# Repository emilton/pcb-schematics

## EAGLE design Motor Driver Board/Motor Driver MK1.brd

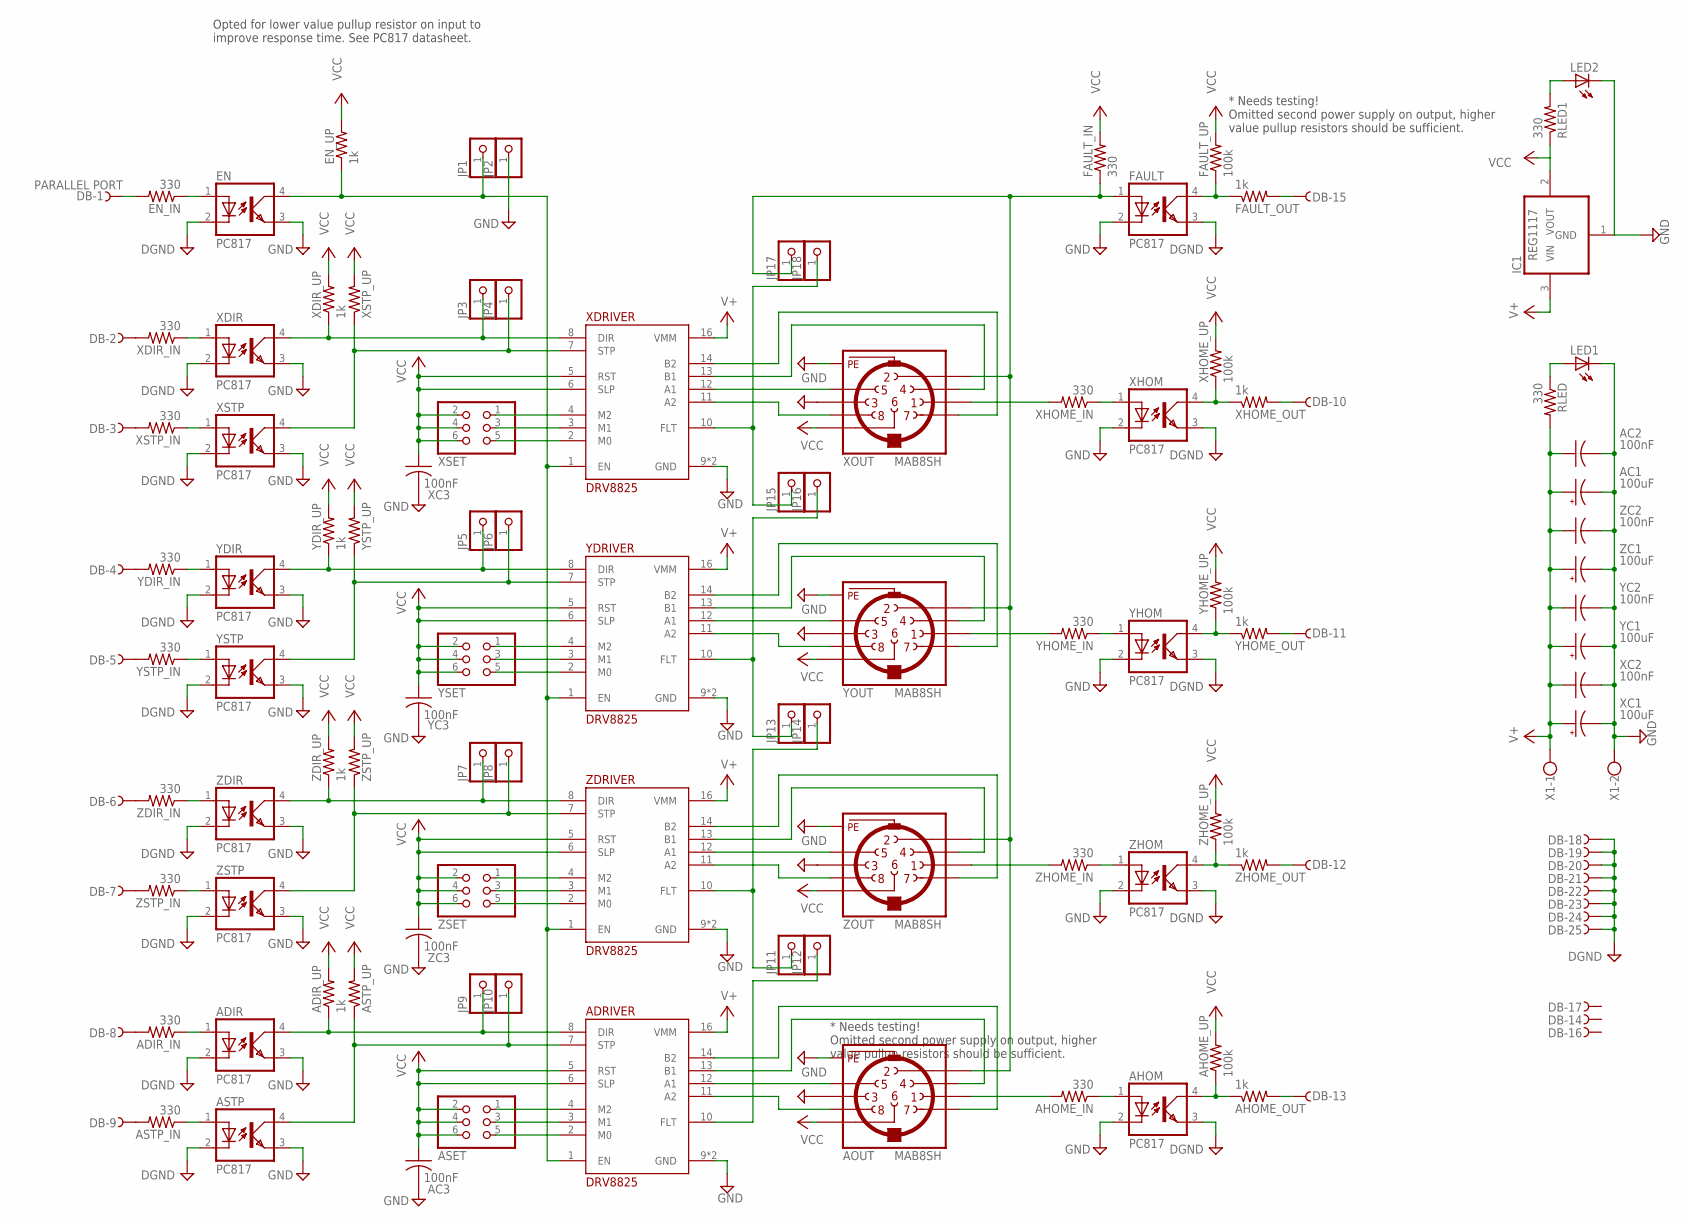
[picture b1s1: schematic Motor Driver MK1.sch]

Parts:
AC1: 100uF; SANYO-OSCON_SMD_E7
AC2, AC3: 100nF; C0805
ADIR: PC817; DIL04
ADIR_IN: 330; R0805
ADIR_UP: 1k; R0805
ADRIVER: DRV8825; DIP16
AHOM: PC817; DIL04
AHOME_IN: 330; R0805
AHOME_OUT: 1k; R0805
AHOME_UP: 100k; R0805
AOUT: MAB8SH
ASET: PINHD-2X3; 2X03
ASTP: PC817; DIL04
ASTP_IN: 330; R0805
ASTP_UP: R-US_R0805; R0805
DB: PARALLEL PORT; H2R25ST
EN: PC817; DIL04
EN_IN: 330; R0805
EN_UP: 1k; R0805
FAULT: PC817; DIL04
FAULT_IN: 330; R0805
FAULT_OUT: 1k; R0805
FAULT_UP: 100k; R0805
IC1: REG1117; SOT223
JP1, JP2, JP3, JP4, JP5, JP6, JP7, JP8, JP9, JP10, JP11, JP12, JP13, JP14, JP15, JP16, JP17, JP18: PINHD-1X1; 1X01
LED1, LED2: LEDCHIP-LED0805; CHIP-LED0805
RLED, RLED1: 330; R0805
X1: W237-102
XC1: 100uF; SANYO-OSCON_SMD_E7
XC2, XC3: 100nF; C0805
XDIR: PC817; DIL04
XDIR_IN: 330; R0805
XDIR_UP: 1k; R0805
XDRIVER: DRV8825; DIP16
XHOM: PC817; DIL04
XHOME_IN: 330; R0805
XHOME_OUT: 1k; R0805
XHOME_UP: 100k; R0805
XOUT: MAB8SH
XSET: PINHD-2X3; 2X03
XSTP: PC817; DIL04
XSTP_IN: 330; R0805
XSTP_UP: R-US_R0805; R0805
YC1: 100uF; SANYO-OSCON_SMD_E7
YC2, YC3: 100nF; C0805
YDIR: PC817; DIL04
YDIR_IN: 330; R0805
YDIR_UP: 1k; R0805
YDRIVER: DRV8825; DIP16
YHOM: PC817; DIL04
YHOME_IN: 330; R0805
YHOME_OUT: 1k; R0805
YHOME_UP: 100k; R0805
YOUT: MAB8SH
YSET: PINHD-2X3; 2X03
YSTP: PC817; DIL04
YSTP_IN: 330; R0805
YSTP_UP: R-US_R0805; R0805
ZC1: 100uF; SANYO-OSCON_SMD_E7
ZC2, ZC3: 100nF; C0805
ZDIR: PC817; DIL04
ZDIR_IN: 330; R0805
ZDIR_UP: 1k; R0805
ZDRIVER: DRV8825; DIP16
ZHOM: PC817; DIL04
ZHOME_IN: 330; R0805
ZHOME_OUT: 1k; R0805
ZHOME_UP: 100k; R0805
ZOUT: MAB8SH
ZSET: PINHD-2X3; 2X03
ZSTP: PC817; DIL04
ZSTP_IN: 330; R0805
ZSTP_UP: R-US_R0805; R0805

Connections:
ASTP_UP: ADRIVER.7 (STP), ASTP.4 (COL), ASTP_UP.1, JP10.1
DGND: ADIR.2 (C), AHOM.3 (EMIT), ASTP.2 (C), DB.18, DB.19, DB.20, DB.21, DB.22, DB.23, DB.24, DB.25, EN.2 (C), FAULT.3 (EMIT), XDIR.2 (C), XHOM.3 (EMIT), XSTP.2 (C), YDIR.2 (C), YHOM.3 (EMIT), YSTP.2 (C), ZDIR.2 (C), ZHOM.3 (EMIT), ZSTP.2 (C)
GND: AC1.-, AC2.2, AC3.2, ADIR.3 (EMIT), ADRIVER.9 (GND), ADRIVER.15 (GND), AHOM.2 (C), AOUT.3, AOUT.PE, AOUT.PE@ (PE), ASTP.3 (EMIT), EN.3 (EMIT), FAULT.2 (C), IC1.1 (GND), JP2.1, LED1.C, LED2.C, X1.2, XC1.-, XC2.2, XC3.2, XDIR.3 (EMIT), XDRIVER.9 (GND), XDRIVER.15 (GND), XHOM.2 (C), XOUT.3, XOUT.PE, XOUT.PE@ (PE), XSTP.3 (EMIT), YC1.-, YC2.2, YC3.2, YDIR.3 (EMIT), YDRIVER.9 (GND), YDRIVER.15 (GND), YHOM.2 (C), YOUT.3, YOUT.PE, YOUT.PE@ (PE), YSTP.3 (EMIT), ZC1.-, ZC2.2, ZC3.2, ZDIR.3 (EMIT), ZDRIVER.9 (GND), ZDRIVER.15 (GND), ZHOM.2 (C), ZOUT.3, ZOUT.PE, ZOUT.PE@ (PE), ZSTP.3 (EMIT)
unnamed: XDRIVER.11 (A2), XOUT.8
unnamed: XDRIVER.12 (A1), XOUT.5
unnamed: XDRIVER.13 (B1), XOUT.4
unnamed: XDRIVER.14 (B2), XOUT.7
unnamed: ADRIVER.12 (A1), AOUT.5
unnamed: YDRIVER.12 (A1), YOUT.5
unnamed: YDRIVER.11 (A2), YOUT.8
unnamed: YDRIVER.13 (B1), YOUT.4
unnamed: YDRIVER.14 (B2), YOUT.7
unnamed: ZDRIVER.12 (A1), ZOUT.5
unnamed: ZDRIVER.11 (A2), ZOUT.8
unnamed: ZDRIVER.13 (B1), ZOUT.4
unnamed: ZDRIVER.14 (B2), ZOUT.7
unnamed: ADRIVER.11 (A2), AOUT.8
unnamed: ADRIVER.13 (B1), AOUT.4
unnamed: ADRIVER.14 (B2), AOUT.7
unnamed: JP4.1, XDRIVER.7 (STP), XSTP.4 (COL), XSTP_UP.1
unnamed: XDRIVER.4 (M2), XSET.1
unnamed: XDRIVER.3 (M1), XSET.3
unnamed: XDRIVER.2 (M0), XSET.5
unnamed: YDRIVER.4 (M2), YSET.1
unnamed: YDRIVER.3 (M1), YSET.3
unnamed: YDRIVER.2 (M0), YSET.5
unnamed: ADRIVER.4 (M2), ASET.1
unnamed: ADRIVER.3 (M1), ASET.3
unnamed: ADRIVER.2 (M0), ASET.5
unnamed: ZDRIVER.4 (M2), ZSET.1
unnamed: ZDRIVER.3 (M1), ZSET.3
unnamed: ZDRIVER.2 (M0), ZSET.5
unnamed: LED2.A, RLED1.2
unnamed: AHOM.1 (A), AHOME_IN.1
unnamed: EN.1 (A), EN_IN.1
unnamed: ADRIVER.1 (EN), EN.4 (COL), EN_UP.1, JP1.1, XDRIVER.1 (EN), YDRIVER.1 (EN), ZDRIVER.1 (EN)
unnamed: JP11.1, JP14.1, ZDRIVER.10 (FLT)
unnamed: XDIR.1 (A), XDIR_IN.1
unnamed: XSTP.1 (A), XSTP_IN.1
unnamed: YDIR.1 (A), YDIR_IN.1
unnamed: YSTP.1 (A), YSTP_IN.1
unnamed: DB.3, XSTP_IN.2
unnamed: DB.2, XDIR_IN.2
unnamed: DB.5, YSTP_IN.2
unnamed: DB.4, YDIR_IN.2
unnamed: ZSTP.1 (A), ZSTP_IN.1
unnamed: ZDIR.1 (A), ZDIR_IN.1
unnamed: AHOM.4 (COL), AHOME_OUT.1, AHOME_UP.1
unnamed: DB.6, ZDIR_IN.2
unnamed: ADIR.1 (A), ADIR_IN.1
unnamed: ASTP_IN.2, DB.9
unnamed: ADIR_IN.2, DB.8
unnamed: ASTP.1 (A), ASTP_IN.1
unnamed: DB.1, EN_IN.2
unnamed: DB.10, XHOME_OUT.2
unnamed: AOUT.2, FAULT.1 (A), FAULT_IN.1, JP17.1, XOUT.2, YOUT.2, ZOUT.2
unnamed: ADIR.4 (COL), ADIR_UP.1, ADRIVER.8 (DIR), JP9.1
unnamed: FAULT.4 (COL), FAULT_OUT.1, FAULT_UP.1
unnamed: DB.15, FAULT_OUT.2
unnamed: JP15.1, JP18.1, XDRIVER.10 (FLT)
unnamed: JP13.1, JP16.1, YDRIVER.10 (FLT)
unnamed: ADRIVER.10 (FLT), JP12.1
unnamed: XHOM.4 (COL), XHOME_OUT.1, XHOME_UP.1
unnamed: XHOM.1 (A), XHOME_IN.1
unnamed: YHOM.1 (A), YHOME_IN.1
unnamed: ZHOM.1 (A), ZHOME_IN.1
unnamed: DB.11, YHOME_OUT.2
unnamed: LED1.A, RLED.1
unnamed: AHOME_OUT.2, DB.13
unnamed: AHOME_IN.2, AOUT.1
unnamed: DB.7, ZSTP_IN.2
unnamed: YHOM.4 (COL), YHOME_OUT.1, YHOME_UP.1
unnamed: ZHOM.4 (COL), ZHOME_OUT.1, ZHOME_UP.1
unnamed: YHOME_IN.2, YOUT.1
unnamed: DB.12, ZHOME_OUT.2
unnamed: XHOME_IN.2, XOUT.1
unnamed: ZHOME_IN.2, ZOUT.1
V+: AC1.+, AC2.1, ADRIVER.16 (VMM), IC1.3 (VIN), RLED.2, X1.1, XC1.+, XC2.1, XDRIVER.16 (VMM), YC1.+, YC2.1, YDRIVER.16 (VMM), ZC1.+, ZC2.1, ZDRIVER.16 (VMM)
VCC: AC3.1, ADIR_UP.2, ADRIVER.5 (RST), ADRIVER.6 (SLP), AHOME_UP.2, AOUT.6, ASET.2, ASET.4, ASET.6, ASTP_UP.2, EN_UP.2, FAULT_IN.2, FAULT_UP.2, IC1.2 (VOUT), RLED1.1, XC3.1, XDIR_UP.2, XDRIVER.5 (RST), XDRIVER.6 (SLP), XHOME_UP.2, XOUT.6, XSET.2, XSET.4, XSET.6, XSTP_UP.2, YC3.1, YDIR_UP.2, YDRIVER.5 (RST), YDRIVER.6 (SLP), YHOME_UP.2, YOUT.6, YSET.2, YSET.4, YSET.6, YSTP_UP.2, ZC3.1, ZDIR_UP.2, ZDRIVER.5 (RST), ZDRIVER.6 (SLP), ZHOME_UP.2, ZOUT.6, ZSET.2, ZSET.4, ZSET.6, ZSTP_UP.2
XSAMPLE: JP3.1, XDIR.4 (COL), XDIR_UP.1, XDRIVER.8 (DIR)
YDIR: JP5.1, YDIR.4 (COL), YDIR_UP.1, YDRIVER.8 (DIR)
YSTP: JP6.1, YDRIVER.7 (STP), YSTP.4 (COL), YSTP_UP.1
ZDIR: JP7.1, ZDIR.4 (COL), ZDIR_UP.1, ZDRIVER.8 (DIR)
ZSTP: JP8.1, ZDRIVER.7 (STP), ZSTP.4 (COL), ZSTP_UP.1

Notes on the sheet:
Opted for lower value pullup resistor on input to improve response time. See PC817 datasheet.
* Needs testing! Omitted second power supply on output, higher value pullup resistors should be sufficient.

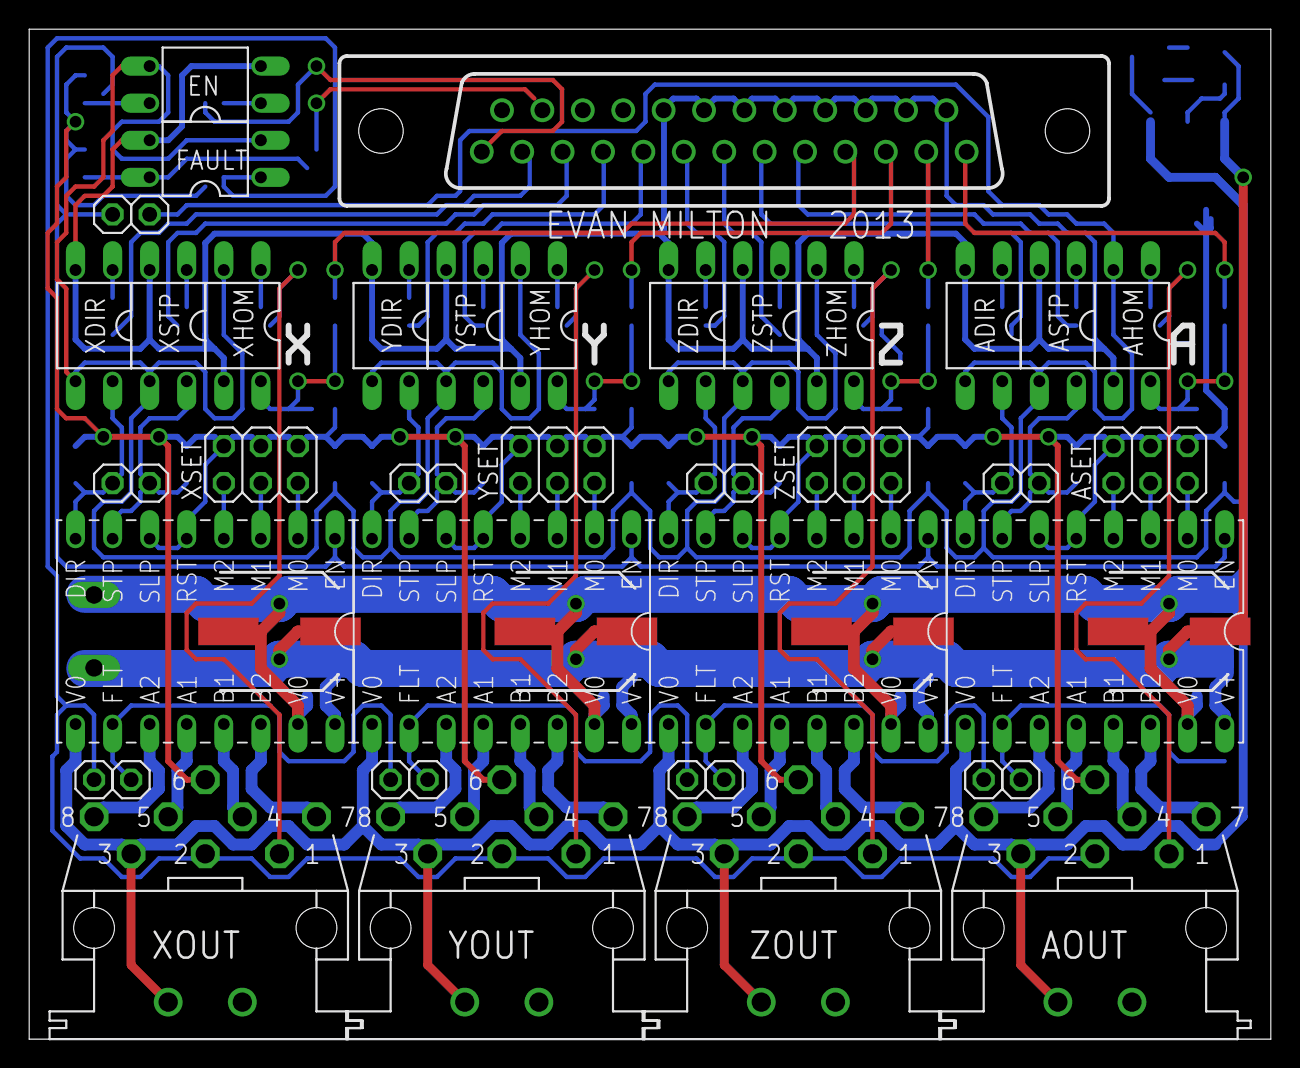
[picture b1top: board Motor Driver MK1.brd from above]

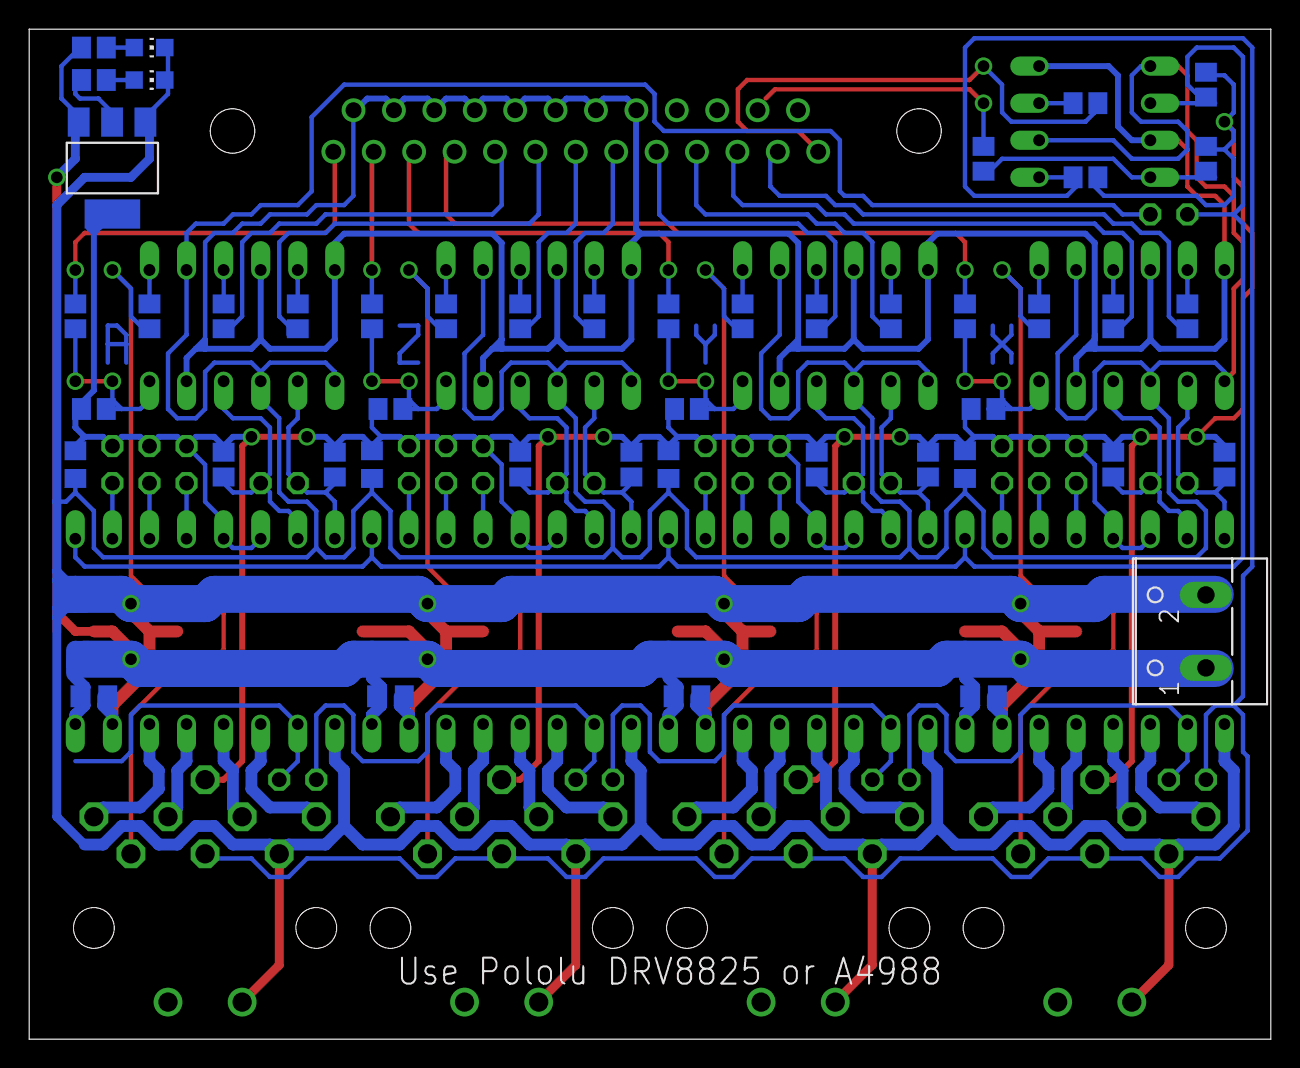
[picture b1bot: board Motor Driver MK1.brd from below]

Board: 2 copper layers, 85.1 x 69.2 mm, 96 parts (47 on the bottom side), 84 nets.

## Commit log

2013-12-23 Began work on board
2013-12-23 finished up schematic
2013-12-24 fleshed out PCB, spent wayyy too much time today.
2013-12-24 Day 2. Everything is lines. How much further can this go?
2013-12-25 added ground plane, 90% finished.
2013-12-28 just trying out the new branch
2013-12-30 MKII is almost complete, cleaned a lot of stuff up.
2013-12-31 Finished up control board. Pending second review.
2013-12-31 8+ hours since last remote commit. Going to let it sit for now.
2014-01-02 added comments, more cleanup.
2014-01-02 Messed around witht the motor control board
2014-02-18 Started fleshing out motor control board v2, looking at spi option
